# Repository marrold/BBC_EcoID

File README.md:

# BBC EcoID

A couple of boards to make setting the Econet Station ID on a BBC Model B Computer easier.

**Note:** Currently untested

## License

- This project is licensed under the MIT license
- [ZiModem](https://github.com/bozimmerman/Zimodem) is licensed under the Apache 2.0 license

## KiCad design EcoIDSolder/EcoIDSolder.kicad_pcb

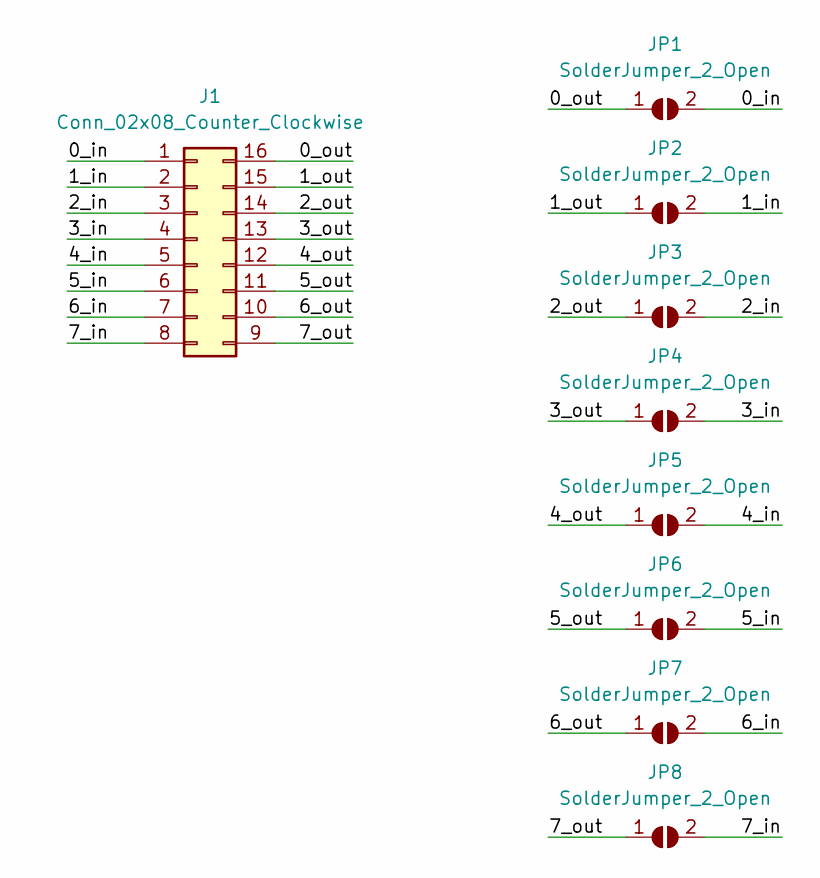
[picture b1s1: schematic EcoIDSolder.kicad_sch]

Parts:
J1: Conn_02x08_Counter_Clockwise; PinSocket_2x08_P2.54mm_Vertical_SMD
JP1, JP2, JP3, JP4, JP5, JP6, JP7, JP8: SolderJumper_2_Open; SolderJumper-2_P1.3mm_Open_TrianglePad1.0x1.5mm

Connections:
/0_in: J1.1, JP1.2 (B)
/0_out: J1.16, JP1.1 (A)
/1_in: J1.2, JP2.2 (B)
/1_out: J1.15, JP2.1 (A)
/2_in: J1.3, JP3.2 (B)
/2_out: J1.14, JP3.1 (A)
/3_in: J1.4, JP4.2 (B)
/3_out: J1.13, JP4.1 (A)
/4_in: J1.5, JP5.2 (B)
/4_out: J1.12, JP5.1 (A)
/5_in: J1.6, JP6.2 (B)
/5_out: J1.11, JP6.1 (A)
/6_in: J1.7, JP7.2 (B)
/6_out: J1.10, JP7.1 (A)
/7_in: J1.8, JP8.2 (B)
/7_out: J1.9, JP8.1 (A)

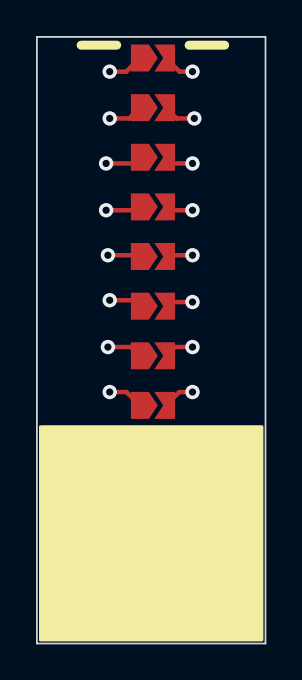
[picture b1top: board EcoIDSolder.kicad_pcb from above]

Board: 2 copper layers, 12.7 x 33.7 mm, 9 parts (1 on the bottom side), 16 nets.

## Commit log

2024-01-05 init
2024-01-05 update gerber output directory
2024-01-12 Refactor solder PCB to same dimensions as switch PCB
